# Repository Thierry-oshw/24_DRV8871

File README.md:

# 24_DRV8871
 Pont H basé sur DRV8871

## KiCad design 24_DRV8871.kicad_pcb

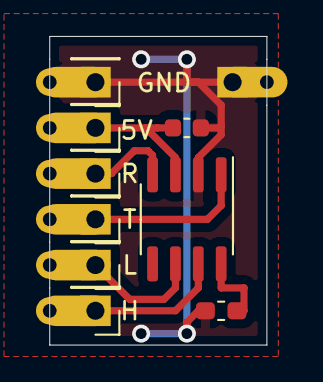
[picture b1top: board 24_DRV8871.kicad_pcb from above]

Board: 2 copper layers, 12.1 x 17.1 mm, 10 parts (1 on the bottom side), 7 nets.

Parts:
C1: 100nF; C_0603_1608Metric
J1, J2, J3, J4, J5, J6: Conn_01x01; Castellated_conn
J7: Conn_01x01; Cast_co_1_905
R1: 10k; R_0603_1608Metric_Pad1.05x0.95mm_HandSolder
U1: MCP2551-I-SN; SOIC-8_3.9x4.9mm_P1.27mm

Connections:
5V: C1.1, J2.1, U1.3 (VDD)
CAN_H: J6.1, U1.7 (CANH)
CAN_L: J5.1, U1.6 (CANL)
CAN_RX: J3.1, U1.4 (RXD)
CAN_TX: J4.1, U1.1 (TXD)
GND: C1.2, J1.1, J7.1, R1.1, U1.2 (VSS)
unnamed: R1.2, U1.8 (Rs)

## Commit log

2023-05-29 schéma
